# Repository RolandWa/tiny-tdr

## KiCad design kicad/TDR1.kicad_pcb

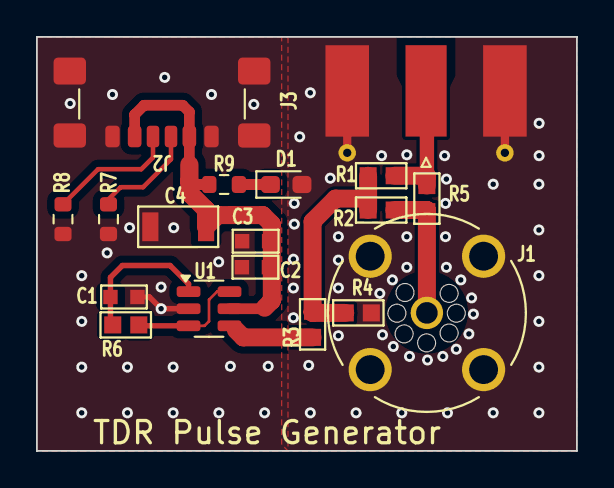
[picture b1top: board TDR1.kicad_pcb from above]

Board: 2 copper layers, 30.0 x 23.0 mm, 18 parts (0 on the bottom side), 11 nets.

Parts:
C1: 1nF; C0603
C2, C3: 100nF; C0603
C4: 2.2uF; 1206
D1: VLMTG1300-GS08; LED_0603_1608Metric_Pad1.05x0.95mm_HandSolder
J1: BNC_MALE_PCB; BNC_LINX_CONBNC001
J2: USB4135-GF-A; USB_C_Receptacle_GCT_USB4135-GF-A_6P_TopMnt_Horizontal
J3: Conn_Coaxial; SMA_Molex_73251-1153_EdgeMount_Horizontal
R1, R2, R5: 49.9; R0603
R3: 130; R0603
R4: 82; R0603
R6: 1.2k; R0603
R7, R8: 5K1; R_0603_1608Metric
R9: 4.70k; R_0603_1608Metric
U1: SN74LVC2G14DBV; SOT-23-6

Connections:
+5V: C2.P$2, C3.P$2, C4.P$2, J2.A9 (VBUS), J2.B9 (VBUS), R9.1, U1.5 (V_{CC})
GND: C1.P$1, C2.P$1, C3.P$1, C4.P$1, D1.2 (K), J1.S1, J1.S2, J1.S3, J1.S4, J2.A12 (GND), J2.B12 (GND), J2.S1 (SHIELD), J3.2 (Ext), R4.P$2, R7.2, R8.2, U1.2 (GND)
unnamed: D1.1 (A), R9.2
unnamed: J2.A5 (CC1), R7.1
unnamed: J2.B5 (CC2), R8.1
unnamed: J3.1 (In), R1.P$2, R5.P$1
unnamed: R1.P$1, R2.P$2, R3.P$2, R4.P$1
unnamed: J1.1, R2.P$1, R5.P$2
unnamed: R3.P$1, U1.4 (2Y)
unnamed: C1.P$2, R6.P$1, U1.1 (1A)
unnamed: R6.P$2, U1.3 (2A), U1.6 (1Y)

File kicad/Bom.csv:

"Reference","Value","Datasheet","Footprint","Qty","DNP","LCSC Part #"
"C1","1nF","","TDR1:C0603","1","","C14663"
"C2,C3","100nF","","TDR1:C0603","2","","C14663"
"C4","2.2uF","","TDR1:1206","1","","C152949"
"D1","VLMTG1300-GS08","","LED_SMD:LED_0603_1608Metric_Pad1.05x0.95mm_HandSolder","1","","C413462"
"J1","BNC_MALE_PCB","","Connector_Coaxial:BNC_LINX_CONBNC001","1","","C6538223"
"J2","USB4135-GF-A","https://www.usb.org/sites/default/files/documents/usb_type-c.zip","Connector_USB:USB_C_Receptacle_GCT_USB4135-GF-A_6P_TopMnt_Horizontal","1","","C2927028"
"J3","Conn_Coaxial","~","Connector_Coaxial:SMA_Molex_73251-1153_EdgeMount_Horizontal","1","","C5859238"
"R1,R2,R5","49.9","","TDR1:R0603","3","","C304761"
"R3","130","","TDR1:R0603","1","","C304699"
"R4","82","","TDR1:R0603","1","","C322011"
"R6","1.2k","","TDR1:R0603","1","","C667536"
"R7,R8","5K1","~","Resistor_SMD:R_0603_1608Metric","2","","C5913162"
"R9","4.70k","","Resistor_SMD:R_0603_1608Metric","1","","C5913221"
"U1","SN74LVC2G14DBV","https://www.ti.com/lit/ds/symlink/sn74lvc2g14.pdf","Package_TO_SOT_SMD:SOT-23-6","1","","C5375976"

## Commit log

2025-04-11 Create KiCad project, change schematic
